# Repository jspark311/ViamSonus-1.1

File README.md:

__     ___                 ____                        
     \ \   / (_) __ _ _ __ ___ / ___|  ___  _ __  _   _ ___ 
      \ \ / /| |/ _` | '_ ` _ \\___ \ / _ \| '_ \| | | / __|
       \ V / | | (_| | | | | | |___) | (_) | | | | |_| \__ \
        \_/  |_|\__,_|_| |_| |_|____/ \___/|_| |_|\__,_|___/

Viam Sonus *("Sound Route")* is an IoT audio multiplexer implemented on top of a Teensy3.1 running ManuvrOS.

----------------------
####What is in this repository:
**./3DModels**: Blender models of the physical pieces that comprise a finished unit.

**./doc**:  Documentation related to this project.
    
**./KiCAD**:  KiCAD project data for building a unit.

**./src**:  Original (unless otherwise specified) source code.

----------------------
####Building the device firmware 

I got sick of tracking the inconsistent behavior of the Arduino IDE, and so Viam Sonus was re-tooled to be buildable with a makefile against the Arduino libraries.

This project has ManuvrOS as a dependency. You will first need to add to this project's source tree:

    git clone https://github.com/Manuvr/ManuvrOS
    cd ManuvrOS*
    mv ManuvrOS StringBuilder DataStructures ..

You will also need the [Teensy3 enhanced i2c library](https://github.com/nox771/i2c_t3). Follow those installation proceedures to get better i2c support. Ultimately, this needs to be fixed in ManuvrOS.

One last step. You will need the [teensy_loader_cli program](https://github.com/PaulStoffregen/teensy_loader_cli) program to flash the controller with the new build. Build it, and place the binary in a place you deem logical, and then update the Makefile to reflect your choice.

The Makefile might need to be changed to reflect the location of your Arduino environment location.

----------------------
####Building the device firmware for a RasPi

This project relies on certain capabilities of the Teensy3.1, but a feature-restricted RasPi build is possible in-principle. If there enough interest, I will post instructions for it.

----------------------
Bitcoin accelerates feature requests and bug fixes. :-)

**16SeqCTSkx7tUj9kXKyzYuVMQ4ghs2HNK**

----------------------
####License
Original code is GPL v2. 

Code adapted from others' work inherrits their license terms, which were preserved in the commentary where it applies. 

----------------------
####Cred:
The ASCII art in this file was generated by [this most-excellent tool](http://patorjk.com/software/taag).

Some of the hardware drivers are adaptions from Adafruit or Teensyduino code. This is noted in each specific class so derived.

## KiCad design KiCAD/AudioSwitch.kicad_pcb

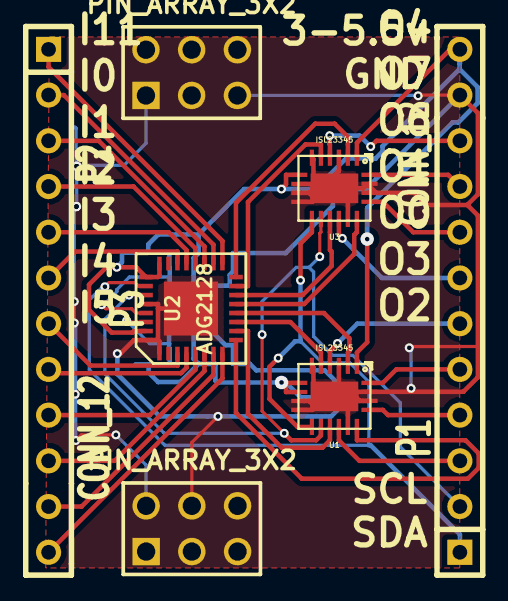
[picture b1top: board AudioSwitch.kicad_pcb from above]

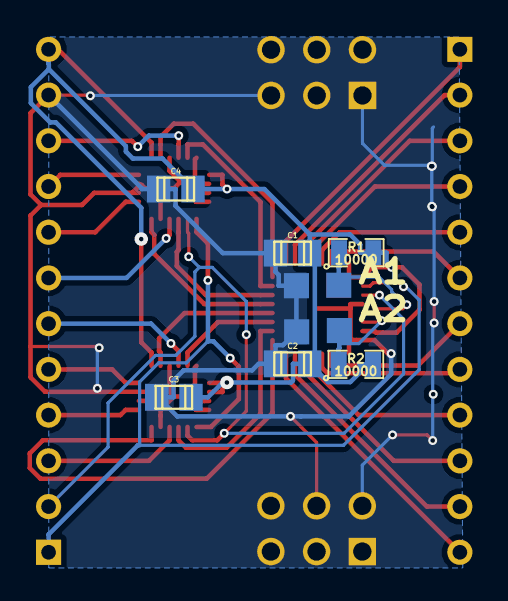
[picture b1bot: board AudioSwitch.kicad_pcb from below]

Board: 2 copper layers, 14 parts (6 on the bottom side), 34 nets.

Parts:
C1: 10uF; c_0805
C2: 100nF; c_0805
C3: 1uF; c_0805
C4: 10nF; c_0805
P1, P2: CONN_12; SIL-12
P3: CONN_2X2; SIL-4
PIN_ARRAY_3X2, PIN_ARRAY_3X2#2: Val**; pin_array_3x2
R1, R2: 10000; SM0805
U1, U3: ISL23345; QFP20-6x4
U2: ADG2128; QFN32

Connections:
/A1: P3.2, R1.1, U2.29
/A2: P3.4, R2.1, U2.30
/SCL: P1.2, U1.12, U2.27, U3.12
/SDA: P1.1, U1.11, U2.26, U3.11
/WIPER_0: P1.5, U1.20
/WIPER_1: P1.6, U1.4
/WIPER_2: P1.3, U1.14
/WIPER_3: P1.4, U1.17
/WIPER_4: P1.9, U3.20
/WIPER_5: P1.10, U3.4
/WIPER_6: P1.7, U3.14
/WIPER_7: P1.8, U3.17
/Y0: U1.16, U2.9
/Y1: U1.13, U2.10
/Y2: U1.5, U2.11
/Y3: U1.2, U2.12
/Y4: U2.13, U3.16
/Y5: U2.14, U3.13
/Y6: U2.15, U3.5
/Y7: U2.16, U3.2
GND: C1.2, C2.2, C3.2, C4.2, P1.11, P3.1, P3.3, PIN_ARRAY_3X2.1, PIN_ARRAY_3X2.2, PIN_ARRAY_3X2.3, PIN_ARRAY_3X2.4, PIN_ARRAY_3X2.5, PIN_ARRAY_3X2.6, PIN_ARRAY_3X2#2.1, PIN_ARRAY_3X2#2.2, PIN_ARRAY_3X2#2.3, PIN_ARRAY_3X2#2.4, PIN_ARRAY_3X2#2.5, PIN_ARRAY_3X2#2.6, U1.3, U1.6, U1.9, U1.10, U1.15, U1.18, U1.19, U2.1, U2.28, U2.32, U2.33, U3.3, U3.6, U3.8, U3.9, U3.10, U3.15, U3.18, U3.19
unnamed: C1.1, C2.1, C3.1, C4.1, P1.12, R1.2, R2.2, U1.1, U1.7, U1.8, U2.24, U2.25, U2.31, U3.1, U3.7
unnamed: P2.10, U2.6
unnamed: P2.7, U2.3
unnamed: P2.6, U2.22
unnamed: P2.5, U2.21
unnamed: P2.4, U2.20
unnamed: P2.2, U2.18
unnamed: P2.12, U2.8
unnamed: P2.11, U2.7
unnamed: P2.8, U2.4
unnamed: P2.9, U2.5
unnamed: P2.1, U2.17
unnamed: P2.3, U2.19

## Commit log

2015-03-11 Initial commit. Only the README and the Blender file for now, until the team hashes out the release of ManuvrOS.
2015-03-16 Initial release of ViamSonus firmware.
2015-03-17 Realized there was Arduino broken-ness left over. Still isn't completely fixed.
2015-03-17 Adding warning about i2c library.
2015-03-17 Loop closed with most-recent ManuvrOS library.
2015-03-21 Broken i2c bus, but I'm pretty sure the problem is in ManuvrOS.
2015-06-19 Fixing bug that caused a nasty hang on boot.
2015-06-19 Reconnecting serial console to the debug functions.
2015-06-21 Separating build process from Arduino IDE. Adding Makefile. Putting source files in locations with less brain-damage.
2015-06-21 Updating README to reflect the abandonment of the Arduino build system.
2015-06-21 Now compiles against audio library.
2015-06-21 Crash fixed. Cause was failure to proc events.
2015-06-22 Janitorial work...
2015-07-04 Making needed adjustments to ViamSonus following message def reduction in ManuvrOS.
2015-07-04 Changes to Makefile.
2015-07-06 Small changes (so far) surrounding transport.
2015-10-08 Removing drivers from ViamSonus before ripping it up.
2015-10-16 Hard-adding ManuvrOS back into projects that extend it. ManuvrOS is being up-ended.
2015-12-11 Removing old version of ManuvrOS and updating .gitignore to skip the symlinks.
2015-12-16 Project is unbuildable. Just finished with the machete. Moving to the scalpel...
2015-12-27 Bringing ViamSonus up-to-date with the recent madness in ManuvrOS.
2015-12-27 Really sloppy merge. Apparently haven't decided about FreeRTOS in this project yet.
2016-09-04 Passing along cleanup to build system. Looks much better now.
2016-09-04 More build fixes. About to move to neglected Manuvr drivers.
2016-09-04 Lifting specificity out of ViamSonus.
2016-09-04 Finally builds.
2016-09-04 More etching-away at the last extant StaticHub.
2016-09-05 Toying with adding crypto.
2016-09-06 Makefile update to levarage shiny new storage class.
2016-09-06 Unified CBOR support.
2016-09-06 Updating DEVLOG.
2016-09-11 Keeping pace....
2016-09-11 Keeping pace...
2016-09-12 No more StaticHub. This was the the last one anywhere.
2016-10-07 Bringing ViamSonus up-to-speed.
2016-10-07 Preparing to run TLS over a serial port.
2016-10-08 Keeping pace with Manuvr...
2016-10-08 Enforcing some uniformity.
2016-10-09 Build system fixes.
2016-10-09 Cleaning up build system.
2016-10-09 Removal of a deprecated namespace.
2016-10-10 Arguments with cryptowrapper.
2016-10-11 Makefile trim.
2016-10-13 Silly makefile mistake.
2016-12-21 Keeping pace with Manuvr.
2016-12-29 Makefile adjustment that was never carried downstream.
2018-07-09 Old dependency change.
